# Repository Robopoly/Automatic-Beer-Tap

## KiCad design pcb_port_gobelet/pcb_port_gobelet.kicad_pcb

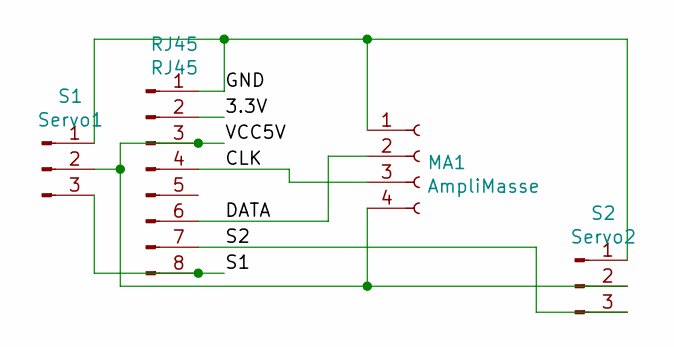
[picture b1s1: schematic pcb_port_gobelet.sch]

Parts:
MA1: AmpliMasse; PinSocket_1x04_P2.54mm_Vertical
RJ45: RJ45; PinHeader_1x08_P2.54mm_Horizontal
S1: Servo1; PinHeader_1x03_P2.54mm_Horizontal
S2: Servo2; PinHeader_1x03_P2.54mm_Vertical

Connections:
/3.3V: RJ45.2
/CLK: MA1.3, RJ45.4
/DATA: MA1.2, RJ45.6
/GND: MA1.1, RJ45.1, S1.1, S2.1
/S1: RJ45.8, S1.3
/S2: RJ45.7, S2.3
/VCC5V: MA1.4, RJ45.3, S1.2, S2.2

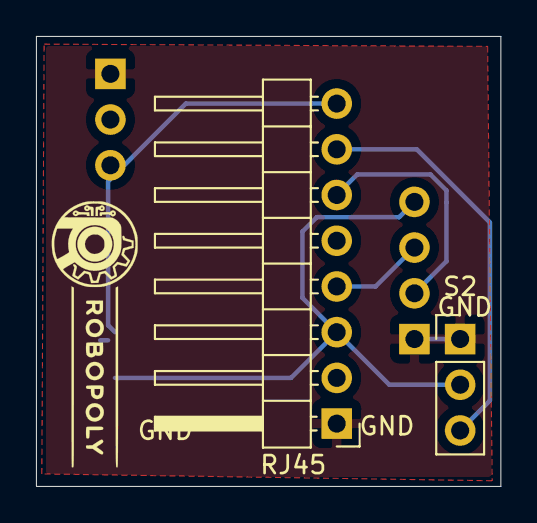
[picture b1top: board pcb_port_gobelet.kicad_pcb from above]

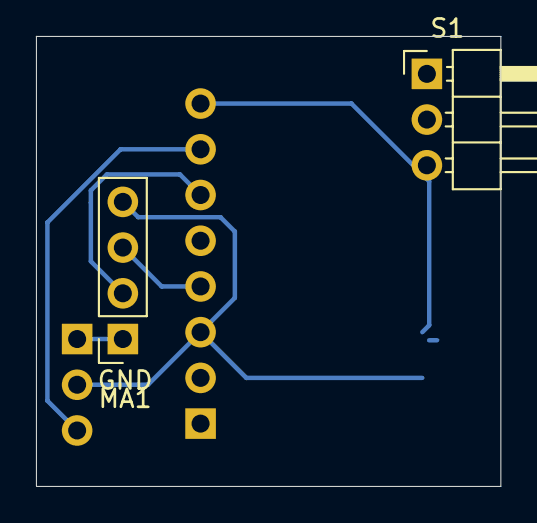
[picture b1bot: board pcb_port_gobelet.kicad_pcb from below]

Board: 2 copper layers, 25.8 x 25.0 mm, 4 parts (2 on the bottom side), 6 nets.

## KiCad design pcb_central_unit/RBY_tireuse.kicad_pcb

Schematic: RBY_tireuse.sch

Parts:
J1: CMD_PAN; PinSocket_2x04_P2.54mm_Vertical
J2: GLASS_0; PinSocket_2x04_P2.54mm_Vertical
J3: GLASS_1; PinSocket_2x04_P2.54mm_Vertical
J4, J5: Conn_01x04_Female; PinSocket_1x04_P2.54mm_Vertical
J6: DCDC_BOOSTER; PinHeader_1x04_P2.54mm_Horizontal
J7: Conn_01x02_Male; PinHeader_1x02_P2.54mm_Horizontal
U2, U3: TMC2208_SILENTSTEPSTICK; MODULE_TMC2208_SILENTSTEPSTICK; PARTREV v11

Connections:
+3.3V: J1.2, J2.2, J3.2, U2.JP2_7, U3.JP2_7; also elsewhere on the board
+5V: J1.4, J2.3, J3.3, J6.4, J7.2; also elsewhere on the board
+12V: J6.2, U2.JP2_1, U3.JP2_1
B1: J1.3; also elsewhere on the board
B2: J1.5; also elsewhere on the board
DIR_0: U2.JP1_1; also elsewhere on the board
DIR_1: U3.JP1_1; also elsewhere on the board
EN_0: U2.JP1_8; also elsewhere on the board
EN_1: U3.JP1_8; also elsewhere on the board
GND: J1.1, J2.1, J3.1, J6.3, J7.1, U2.JP2_2, U2.JP2_8, U3.JP2_2, U3.JP2_8; also elsewhere on the board
GNDPWR: J6.1
I2C_CLK: J1.7; also elsewhere on the board
I2C_DATA: J1.8; also elsewhere on the board
unnamed: J4.1, U2.JP2_3
unnamed: J4.2, U2.JP2_4
unnamed: J4.3, U2.JP2_5
unnamed: J4.4, U2.JP2_6
unnamed: J5.1, U3.JP2_3
unnamed: J5.2, U3.JP2_4
unnamed: J5.3, U3.JP2_5
unnamed: J5.4, U3.JP2_6
PULS_0: U2.JP1_2; also elsewhere on the board
PULS_1: U3.JP1_2; also elsewhere on the board
P_CLK_0: J2.4; also elsewhere on the board
P_CLK_1: J3.4; also elsewhere on the board
P_DATA_0: J2.6; also elsewhere on the board
P_DATA_1: J3.6; also elsewhere on the board
S1_0: J2.8; also elsewhere on the board
S1_1: J3.8; also elsewhere on the board
S2_0: J2.7; also elsewhere on the board
S2_1: J3.7; also elsewhere on the board

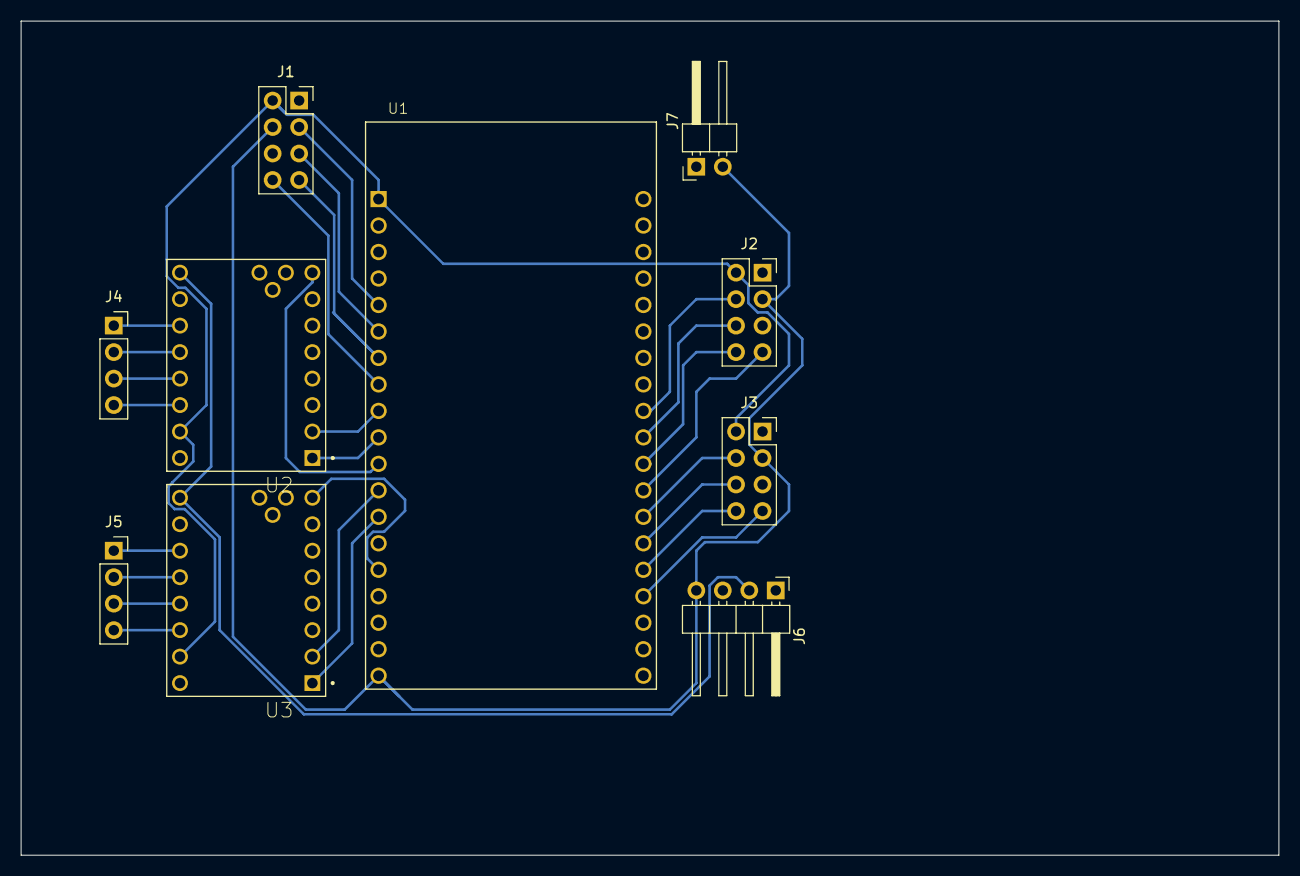
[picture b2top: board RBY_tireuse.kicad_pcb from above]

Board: 2 copper layers, 120.6 x 80.0 mm, 10 parts (0 on the bottom side), 30 nets.

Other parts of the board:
U1: ESP32-DEVKITC-32D; MODULE_ESP32-DEVKITC-32D

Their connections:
+3.3V: U1.1; also elsewhere on the board
+5V: U1.19; also elsewhere on the board
B1: U1.5; also elsewhere on the board
B2: U1.6; also elsewhere on the board
DIR_0: U1.10; also elsewhere on the board
DIR_1: U1.13; also elsewhere on the board
EN_0: U1.11; also elsewhere on the board
EN_1: U1.15; also elsewhere on the board
GND: U1.14, U1.20, U1.26; also elsewhere on the board
I2C_CLK: U1.7; also elsewhere on the board
I2C_DATA: U1.8; also elsewhere on the board
PULS_0: U1.9; also elsewhere on the board
PULS_1: U1.12; also elsewhere on the board
P_CLK_0: U1.28; also elsewhere on the board
P_CLK_1: U1.32; also elsewhere on the board
P_DATA_0: U1.29; also elsewhere on the board
P_DATA_1: U1.33; also elsewhere on the board
S1_0: U1.30; also elsewhere on the board
S1_1: U1.34; also elsewhere on the board
S2_0: U1.31; also elsewhere on the board
S2_1: U1.35; also elsewhere on the board

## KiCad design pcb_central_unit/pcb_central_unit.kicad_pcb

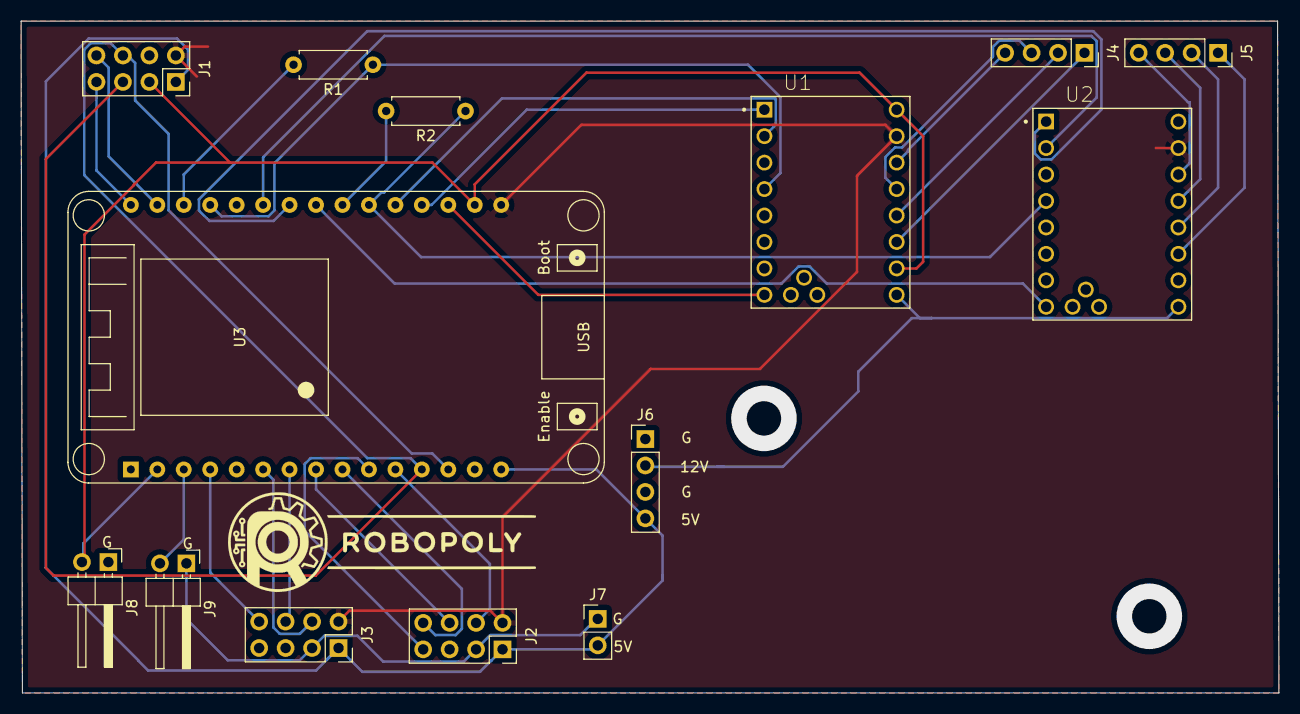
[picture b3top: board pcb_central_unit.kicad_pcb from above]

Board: 2 copper layers, 120.8 x 64.5 mm, 14 parts (0 on the bottom side), 35 nets.

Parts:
J1: CMD_PAN; PinSocket_2x04_P2.54mm_Vertical
J2: GLASS_0; PinSocket_2x04_P2.54mm_Vertical
J3: GLASS_1; PinSocket_2x04_P2.54mm_Vertical
J4: STEPPER_0; PinSocket_1x04_P2.54mm_Vertical
J5: STEPPER_1; PinSocket_1x04_P2.54mm_Vertical
J6: DCDC_BOOSTER; PinHeader_1x04_P2.54mm_Vertical
J7: ALIM_5V; PinHeader_1x02_P2.54mm_Vertical
J8: SPARE_GPIO_0; PinHeader_1x02_P2.54mm_Horizontal
J9: SPARE_GPIO_1; PinHeader_1x02_P2.54mm_Horizontal
R1, R2: 1kOHM; R_Axial_DIN0207_L6.3mm_D2.5mm_P7.62mm_Horizontal
U1, U2: TMC2208_SILENTSTEPSTICK-TMC2208_SILENTSTEPSTICK; MODULE_TMC2208_SILENTSTEPSTICK
U3: ESP32_DevKit_V1_DOIT_30_pin; esp32_devkit_v1_doit

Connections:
+3.3V: J1.2, J2.2, J3.2, U1.JP2_7, U2.JP2_7, U3.16
+5V: J1.1, J2.1, J3.1, J6.4, J7.2, U3.15
+12V: J6.2, U1.JP2_1, U2.JP2_1
B1: J1.5, U3.12
B2: J1.6, U3.13
DIR_0: U1.JP1_1, U3.19
DIR_1: U2.JP1_1, U3.24
EN_0: U1.JP1_8, U3.18
EN_1: U2.JP1_8, U3.23
GND: J1.3, J2.3, J3.3, J6.1, J6.3, J7.1, J8.1, J9.1, U1.JP2_2, U1.JP2_8, U2.JP2_2, U2.JP2_8, U3.14, U3.17
I2C_CLK: J1.7, U3.30
I2C_DATA: J1.8, U3.29
unnamed: J4.1, U1.JP2_3
unnamed: J4.2, U1.JP2_4
unnamed: J4.3, U1.JP2_5
unnamed: J4.4, U1.JP2_6
unnamed: J5.1, U2.JP2_3
unnamed: J5.2, U2.JP2_4
unnamed: J5.3, U2.JP2_5
unnamed: J5.4, U2.JP2_6
unnamed: J8.2, U3.2
unnamed: J9.2, U3.3
unnamed: R1.2, U3.28
unnamed: R2.2, U3.22
PULS_0: U1.JP1_2, U3.20
PULS_1: U2.JP1_2, U3.25
P_CLK_0: J2.4, U3.11
P_CLK_1: J3.4, U3.6
P_DATA_0: J2.6, U3.8
P_DATA_1: J3.6, U3.7
S1_0: J2.8, U3.9
S1_1: J3.8, U3.4
S2_0: J2.7, U3.10
UART_0: R1.1, U1.JP1_4, U3.27
UART_1: R2.1, U2.JP1_4, U3.21

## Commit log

2021-04-09 Add first pcb for tireuse
2021-04-09 Update PCB after v1
2021-04-09 PCB V2
2021-04-09 PCB V2.1
2021-04-10 PCB v2.5
